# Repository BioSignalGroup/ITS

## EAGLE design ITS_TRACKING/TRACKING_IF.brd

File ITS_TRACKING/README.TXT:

TRACKING_IF BOARD

FR4; .062"; 2" X 4"; 2SIDES

EXTENSIONS

*.CMP	COMPONENT ETCH
*.SOL	SOLDER SIDE ETCH
*.STC	COMPONENT MASK
*.STS	SOLDER SIDE MASK
*.PLC	COMPONENT SIDE SILK AND OUTLINE
*.DRD	EXCELLON DRILL DATA
*.DRI	DRILL INFORMATION

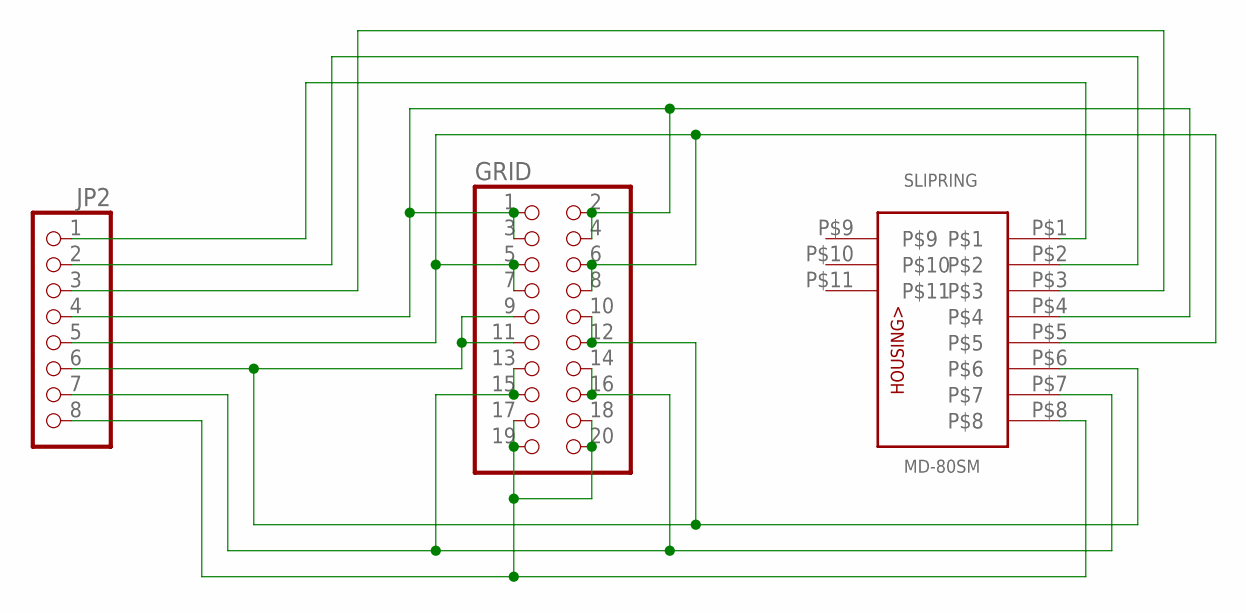
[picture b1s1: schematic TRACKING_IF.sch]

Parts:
GRID: PINHD-2X10; 2X10
JP2: PINHD-1X8; 1X08
SLIPRING: MD-80SM; MINIDIN8PCB

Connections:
unnamed: GRID.1, GRID.2, GRID.3, GRID.4, JP2.4, SLIPRING.P$4
unnamed: JP2.2, SLIPRING.P$2
unnamed: GRID.5, GRID.6, GRID.7, GRID.8, JP2.5, SLIPRING.P$5
unnamed: GRID.17, GRID.18, GRID.19, GRID.20, JP2.8, SLIPRING.P$8
unnamed: JP2.1, SLIPRING.P$1
unnamed: JP2.3, SLIPRING.P$3
unnamed: GRID.9, GRID.10, GRID.11, GRID.12, JP2.6, SLIPRING.P$6
unnamed: GRID.13, GRID.14, GRID.15, GRID.16, JP2.7, SLIPRING.P$7

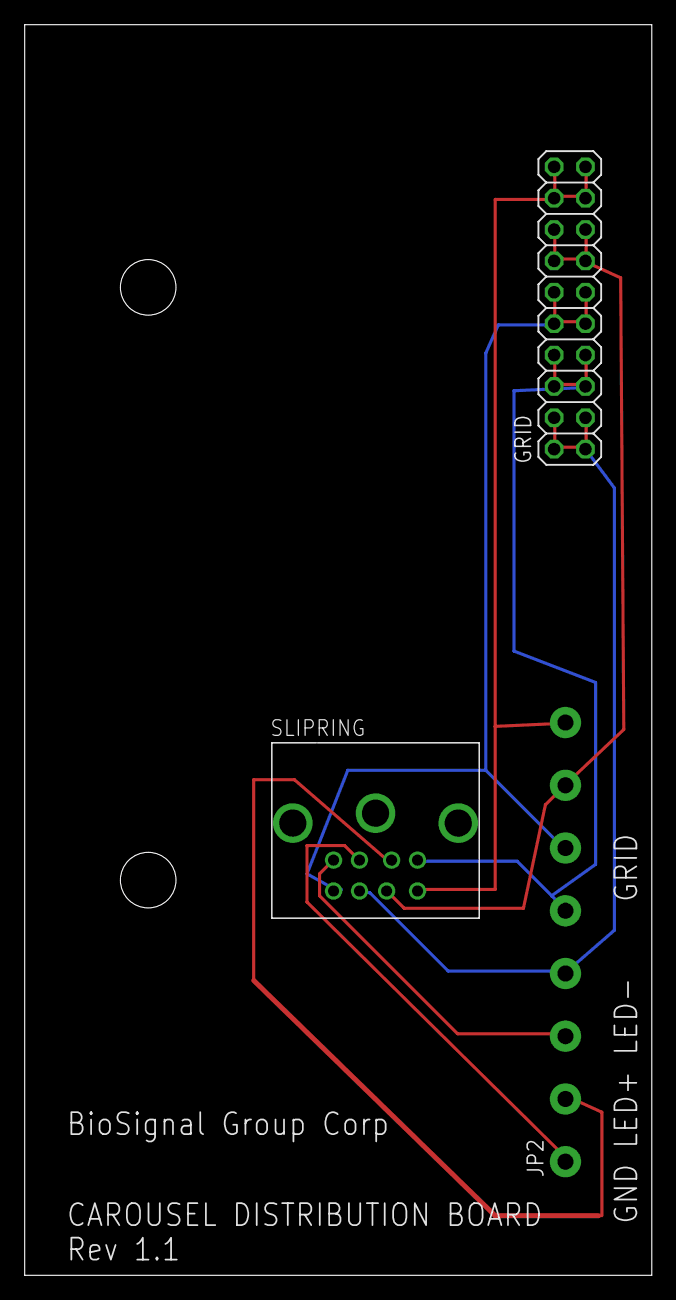
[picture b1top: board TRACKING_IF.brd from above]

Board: 2 copper layers, 50.8 x 101.3 mm, 3 parts (0 on the bottom side), 8 nets.
